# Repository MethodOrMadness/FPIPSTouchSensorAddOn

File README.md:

# FPIPSTouchSensorAddOn
So there is an issue, apparently FP ribbons dont like a short to ground, and requires a delay. It should still function if you populate u3, c3, and c6 and use a touch sensor on it though

an optional, semi-customizable board to add touch sensors to a funnyplaying AGB IPS screen ribbon, instead of using the SEL+R/L button combination

You can think of the touch sensors connected to P1 and P2 as "momentary" buttons, where as the touch sesnor on P3 act as a "toggle" switch(tap once to enable, tap again to disable)

I havent yet built this, I cannot verify that it actually works as intended, for building and installation I suggest referring to the schematic file, as it contains some notes.

## BOM

| RefDes | Part | Spec Sheet|
|--------|-----|------------|
|U1,U2,U3|TTP223-ba6| https://datasheet.lcsc.com/szlcsc/TTP223-BA6_C80757.pdf |
|C1,C2,C3|22pF Capacitor| N/A |
|C4,C5,C6|0.1uF Capacitor| N/A|

## Connections
| Pad |  Destination  |
|-----|---------------|
| TP1 | L On FP Ribbon|
| TP2 | R On FP Ribbon|
| TP3 | SEL On FP Ribbon|
| TP4 | 3.3v on AGB |
| TP5 | optinonal, tie to ground if you dont populate U3, C3, and C6 |
| TP6 | GND On FP Ribbon |
| P1 | Touch Sensor for decreasing brightness |
| P2 | Touch Sensor for increasing brightness |
| P3 | Touch sensor for select(optional, only needed if you populate U3, C3, and C6) |

## Notes
This should, in theory, work on other IPS kits too, though the connections might be different, I based this off of the FP kit.

## Credits
Zekfoo for catching some mistakes I made during the original board design process and for a third touch sensor(optinal) for the SEL pad

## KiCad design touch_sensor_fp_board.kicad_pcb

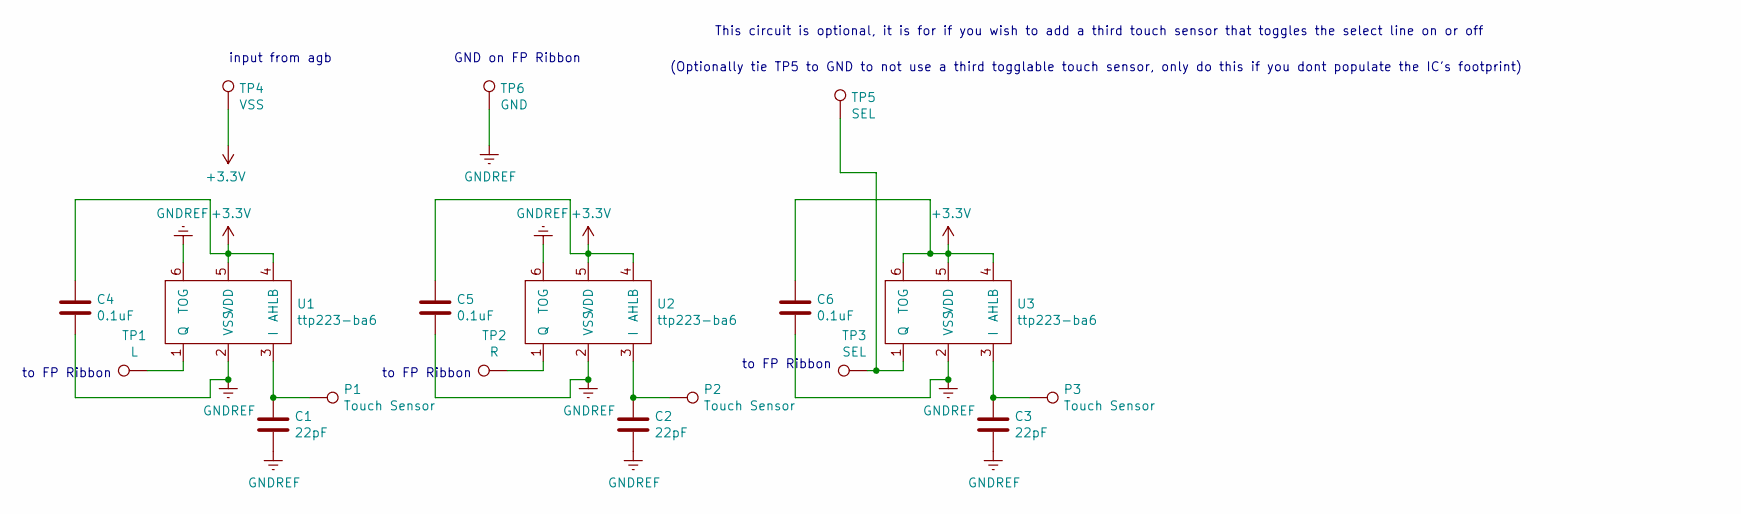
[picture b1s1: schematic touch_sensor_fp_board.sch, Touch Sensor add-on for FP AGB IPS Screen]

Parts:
C1, C2, C3: 22pF; C_0402_1005Metric_Pad0.74x0.62mm_HandSolder
C4, C5, C6: 0.1uF; C_0402_1005Metric_Pad0.74x0.62mm_HandSolder
P1, P2, P3: Touch Sensor; TestPoint_Pad_4.0x4.0mm
TP1: L; TestPoint_Pad_4.0x4.0mm
TP2: R; TestPoint_Pad_4.0x4.0mm
TP3, TP5: SEL; TestPoint_Pad_4.0x4.0mm
TP4: VSS; TestPoint_Pad_4.0x4.0mm
TP6: GND; TestPoint_Pad_4.0x4.0mm
U1, U2, U3: ttp223-ba6; SOT-23-6_Handsoldering

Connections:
+3V3: C4.1, C5.1, C6.1, TP4.1, U1.4 (AHLB), U1.5 (VDD), U2.4 (AHLB), U2.5 (VDD), U3.4 (AHLB), U3.5 (VDD), U3.6 (TOG)
GNDREF: C1.2, C2.2, C3.2, C4.2, C5.2, C6.2, TP6.1, U1.2 (VSS), U1.6 (TOG), U2.2 (VSS), U2.6 (TOG), U3.2 (VSS)
unnamed: C1.1, P1.1, U1.3 (I)
unnamed: C2.1, P2.1, U2.3 (I)
unnamed: C3.1, P3.1, U3.3 (I)
unnamed: TP1.1, U1.1 (Q)
unnamed: TP2.1, U2.1 (Q)
unnamed: TP3.1, TP5.1, U3.1 (Q)

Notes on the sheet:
input from agb
GND on FP Ribbon
(Optionally tie TP5 to GND to not use a third togglable touch sensor, only do this if you dont populate the IC's footprint)
to FP Ribbon
This circuit is optional, it is for if you wish to add a third touch sensor that toggles the select line on or off

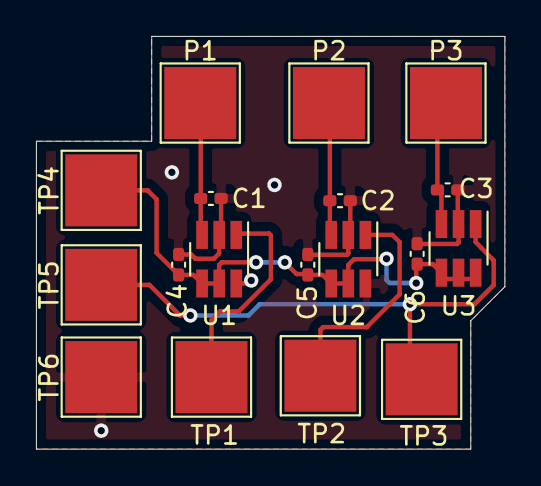
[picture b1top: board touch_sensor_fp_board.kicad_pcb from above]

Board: 2 copper layers, 26.0 x 22.9 mm, 18 parts (0 on the bottom side), 8 nets.

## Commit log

2021-11-01 BOM
    BOM is in CSV format in the repo, but figured id add it here just incase, for easy refrencing
2021-11-01 Added pinout and other info
2021-11-01 updated wording on schematic
2021-11-01 updated credits
2021-11-01 fixed credits because idk readme ig
2021-11-01 added links to images(images not added yet)
2021-11-01 added images of PCB
2021-11-01 notes
2022-08-23 Update README.md
    idk why i worded it the way i did originally

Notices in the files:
touch_sensor_fp_board.sch:
GPLv3
